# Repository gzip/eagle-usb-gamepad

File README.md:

# Classic Gamepad USB Adapter

This hardware and software allows you to connect your favorite classic gamepad to use as a joystick on your computer. The design is based on work from [raphnet.net](http://raphnet.net/electronique/electronique_en.php#1) and is completely open. The following configurations are supported:

- Four NES and/or SNES gamepads
- One N64 or Gamecube gamepad
- One Genesis or Atari gamepad

Connector footprints are also available for NES, SNES, and N64 under the [breakouts](./breakouts/) folder.

# Availability

Boards available at [OSH Park](https://www.oshpark.com/shared_projects/oCdHAtTx).

Kits available at [Tindie](https://www.tindie.com/products/gzip/classic-gamepad-usb-adapter/).

## License

All hardware and software is derivative of raphnet.net and is therefore GPL. The [breakout boards](./breakouts/) are original works and licensed under [Creative Commons Share Alike](http://creativecommons.org/licenses/by-sa/4.0/).

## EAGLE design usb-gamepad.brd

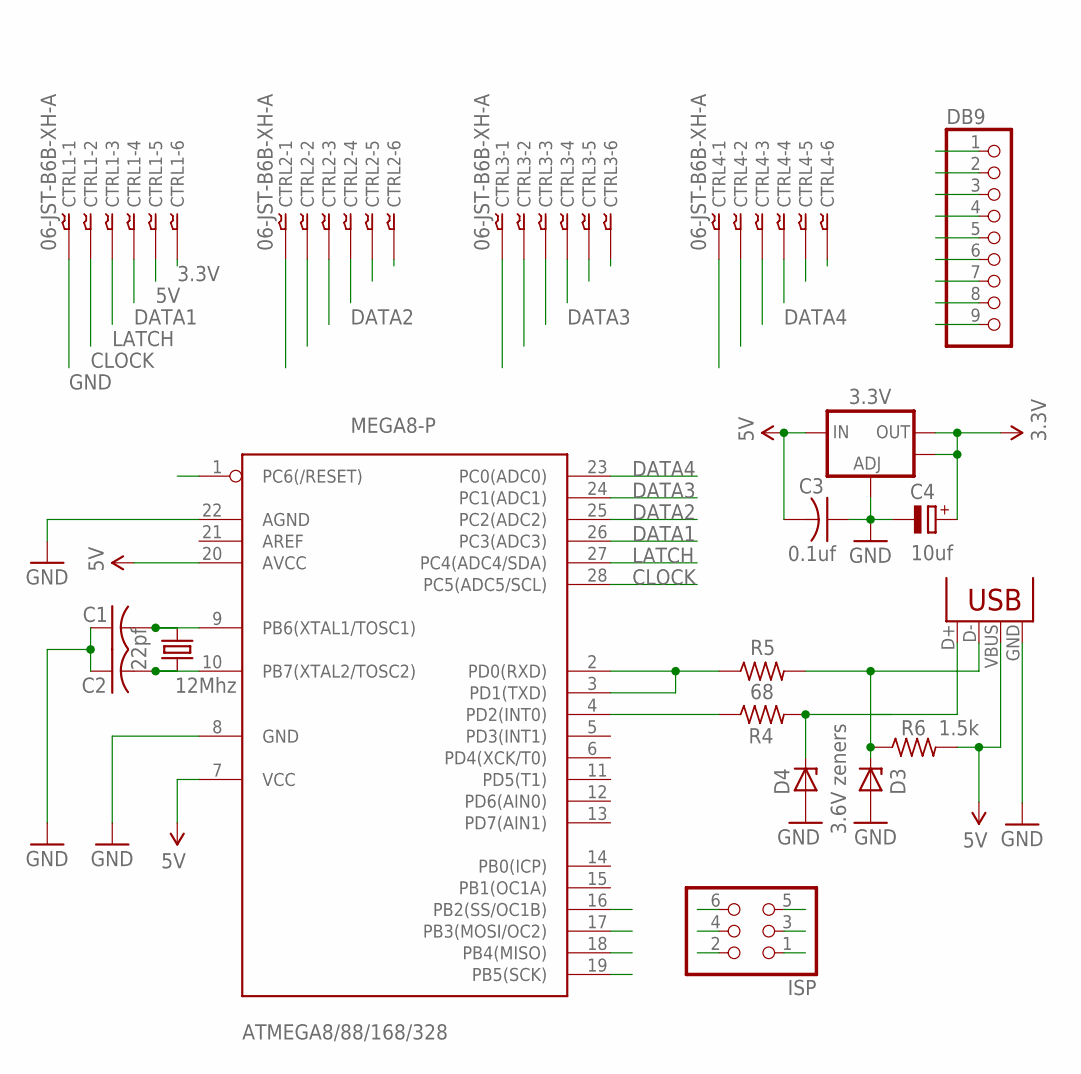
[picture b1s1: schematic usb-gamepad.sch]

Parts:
3.3V: V_REG_LM1117SOT223; SOT223
ATMEGA8/88/168/328: MEGA8-P; DIL28-3
C1, C2: 22pf; C025-025X050
C3: 0.1uf; C025-025X050
C4: 10uf; E2,5-5
CTRL1, CTRL2, CTRL3, CTRL4: 06-JST-B6B-XH-A; B6B-XH
D3: 3.6V zeners; DO41Z10
D4: 3.6V; DO41Z10
DB9: PINHD-1X9; 1X09
ISP: PINHD-2X3; 2X03
Q1: 12Mhz; HC49/S
R4, R5: 68; 0207/10
R6: 1.5k; 0207/10
USB: USBPTH; USB-B-PTH

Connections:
3.3V: 3.3V.2 (OUT), 3.3V.4 (OUT), C4.+, CTRL1.P$6, CTRL2.P$6, CTRL3.P$6, CTRL4.P$6
5V: 3.3V.3 (IN), ATMEGA8/88/168/328.7 (VCC), ATMEGA8/88/168/328.20 (AVCC), C3.2, CTRL1.P$5, CTRL2.P$5, CTRL3.P$5, CTRL4.P$5, DB9.5, ISP.2, R6.2, USB.VBUS
CLOCK: ATMEGA8/88/168/328.28 (PC5(ADC5/SCL)), CTRL1.P$2, CTRL2.P$2, CTRL3.P$2, CTRL4.P$2, DB9.1
D+: D4.C, R4.2, USB.D+
D-: D3.C, R5.2, R6.1, USB.D-
DATA1: ATMEGA8/88/168/328.26 (PC3(ADC3)), CTRL1.P$4, DB9.3
DATA2: ATMEGA8/88/168/328.25 (PC2(ADC2)), CTRL2.P$4, DB9.4
DATA3: ATMEGA8/88/168/328.24 (PC1(ADC1)), CTRL3.P$4, DB9.6
DATA4: ATMEGA8/88/168/328.23 (PC0(ADC0)), CTRL4.P$4, DB9.7
GND: 3.3V.1 (ADJ), ATMEGA8/88/168/328.8 (GND), ATMEGA8/88/168/328.22 (AGND), C1.1, C2.1, C3.1, C4.-, CTRL1.P$1, CTRL2.P$1, CTRL3.P$1, CTRL4.P$1, D3.A, D4.A, DB9.8, ISP.6, USB.GND
LATCH: ATMEGA8/88/168/328.27 (PC4(ADC4/SDA)), CTRL1.P$3, CTRL2.P$3, CTRL3.P$3, CTRL4.P$3, DB9.2
MISO: ATMEGA8/88/168/328.18 (PB4(MISO)), ISP.1
MOSI: ATMEGA8/88/168/328.17 (PB3(MOSI/OC2)), ISP.4
unnamed: ATMEGA8/88/168/328.10 (PB7(XTAL2/TOSC2)), C2.2, Q1.1
unnamed: ATMEGA8/88/168/328.9 (PB6(XTAL1/TOSC1)), C1.2, Q1.2
unnamed: ATMEGA8/88/168/328.2 (PD0(RXD)), ATMEGA8/88/168/328.3 (PD1(TXD)), R5.1
unnamed: ATMEGA8/88/168/328.4 (PD2(INT0)), R4.1
RESET: ATMEGA8/88/168/328.1 (PC6(/RESET)), ISP.5
SCK: ATMEGA8/88/168/328.19 (PB5(SCK)), DB9.9, ISP.3
SS: ATMEGA8/88/168/328.16 (PB2(SS/OC1B))

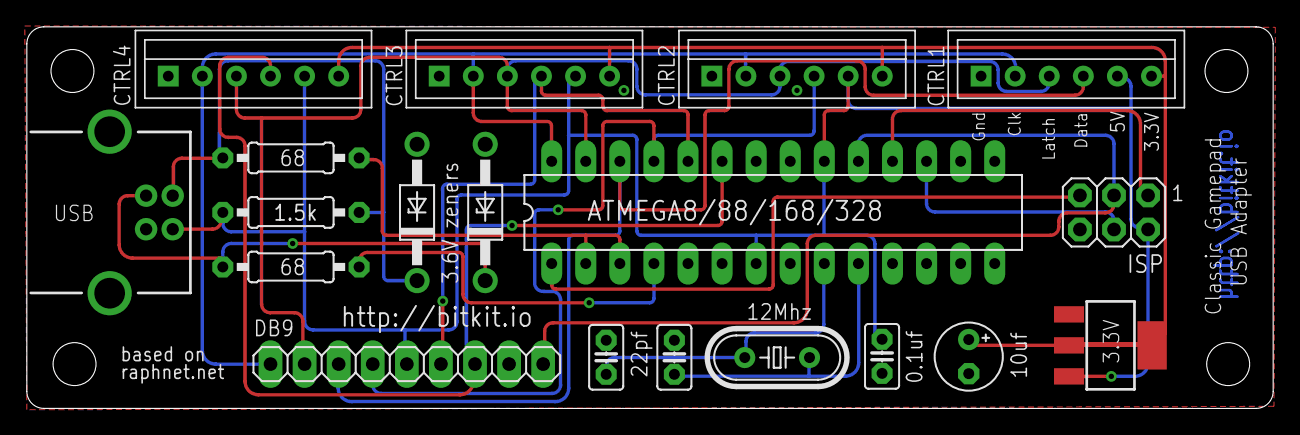
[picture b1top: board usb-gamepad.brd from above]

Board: 2 copper layers, 92.9 x 28.4 mm, 19 parts (0 on the bottom side), 19 nets.

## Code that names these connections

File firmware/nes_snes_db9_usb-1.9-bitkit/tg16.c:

/* TG16 to USB
 * Copyright (C) 2006-2011 Raphaël Assénat
 *
 * This program is free software; you can redistribute it and/or modify
 * it under the terms of the GNU General Public License as published by
 * the Free Software Foundation; either version 2 of the License, or
 * (at your option) any later version.
 *
 * This program is distributed in the hope that it will be useful,
 * but WITHOUT ANY WARRANTY; without even the implied warranty of
 * MERCHANTABILITY or FITNESS FOR A PARTICULAR PURPOSE.  See the
 * GNU General Public License for more details.
 *
 * You should have received a copy of the GNU General Public License along
 * with this program; if not, write to the Free Software Foundation, Inc.,
 * 51 Franklin Street, Fifth Floor, Boston, MA 02110-1301 USA.
 *
 * The author may be contacted at raph@raphnet.net
 */
#include <avr/io.h>
#include <avr/interrupt.h>
#include <avr/pgmspace.h>

#include <util/delay.h>
#include <string.h>

#include "usbdrv.h"
#include "usbconfig.h"
#include "gamepad.h"
#include "leds.h"
#include "tg16.h"

#define REPORT_SIZE		3
#define GAMEPAD_BYTES	3

/* for chaning IO easily */


#define SET_SELECT()	PORTC |= 0x02
#define CLR_SELECT()	PORTC &= ~0x02

/* Active low */
#define SET_OE()		PORTC &= ~0x01
#define CLR_OE()		PORTC |= 0x01


/*********** prototypes *************/
static char tg16_Init(void);
static void tg16_Update(void);

// the most recent bytes we fetched from the controller
static unsigned char last_read_controller_bytes[REPORT_SIZE];
// the most recently reported bytes
static unsigned char last_reported_controller_bytes[REPORT_SIZE];

static unsigned char readController()
{
	unsigned char a,b;

	/* 
	 * --- tg16 specific pinout ---
	 *  inputs...
	 * PC5: /Up or /I
	 * PC4: /Right or /II
	 * PC3: /South or /Select
	 * PC2: /Left or /Run
	 *
	 *  outputs...
	 * PC1: Data select
	 * PC0: /OE
	 */

	SET_OE();
	_delay_ms(1);

	SET_SELECT();
	_delay_ms(1);
	a = (PINC & 0x3c) >> 2;

	CLR_SELECT();
	_delay_ms(1);		
	b = (PINC & 0x3c) >> 2;

	CLR_OE();

	return a | (b<<4);
}

static char tg16_Init(void)
{
	unsigned char sreg;
	sreg = SREG;
	cli();

	DDRB |= 0x02; // Bit 1 out
	PORTB &= ~0x02; // 0

	/* 
	 * --- tg16 specific pinout ---
	 *  inputs...
	 * PC5: /Up or /I
	 * PC4: /Right or /II
	 * PC3: /South or /Select
	 * PC2: /Left or /Run
	 *
	 *  outputs...
	 * PC1: Data select
	 * PC0: /OE
	 */

	DDRC &= ~0x3c; 
	PORTC |= 0x3c;

	/* disable OE and init DataSelect to 1 */
	PORTC |= 0x03;
	DDRC |= 0x03;
	
	tg16_Update();

	SREG = sreg;

	return 0;
}



static void tg16_Update(void)
{
	unsigned char data;
	int x=128,y=128;
	
	/* 7: I
	 * 6: II
	 * 5: Select
	 * 4: Run
	 *
	 * 3: Up
	 * 2: Right
	 * 1: Down
	 * 0: Left
	 */
	data = readController();

	/* Buttons are active low. Invert values. */
	data ^= 0xff;

	if (data & 0x08) { y = 0; } // up
	if (data & 0x02) { y = 255; } //down
	if (data & 0x01) { x = 0; }  // left
	if (data & 0x04) { x = 255; } // right

	last_read_controller_bytes[0]=x;
	last_read_controller_bytes[1]=y;
 
 	last_read_controller_bytes[2]=0;

	if (data & 0x80) 
		last_read_controller_bytes[2] |= 0x01;
	if (data & 0x40)
		last_read_controller_bytes[2] |= 0x02;
	if (data & 0x20)
		last_read_controller_bytes[2] |= 0x04;
	if (data & 0x10)
		last_read_controller_bytes[2] |= 0x08;

}	

static char tg16_Changed(char id)
{
	static int first = 1;
	if (first) { first = 0;  return 1; }
	
	return memcmp(last_read_controller_bytes, 
					last_reported_controller_bytes, GAMEPAD_BYTES);
}

static char tg16_BuildReport(unsigned char *reportBuffer, char id)
{
	if (reportBuffer != NULL)
	{
		memcpy(reportBuffer, last_read_controller_bytes, GAMEPAD_BYTES);
	}
	memcpy(last_reported_controller_bytes, 
			last_read_controller_bytes, 
			GAMEPAD_BYTES);	

	return REPORT_SIZE;
}

#include "snes_descriptor.c"

#define USBDESCR_DEVICE         1

// This is the same descriptor as in devdesc.c, but with a different VID/PID

const char tg16_usbDescrDevice[] PROGMEM = {    /* USB device descriptor */
    18,         /* sizeof(usbDescrDevice): length of descriptor in bytes */
    USBDESCR_DEVICE,    /* descriptor type */
    0x01, 0x01, /* USB version supported */
    USB_CFG_DEVICE_CLASS,
    USB_CFG_DEVICE_SUBCLASS,
    0,          /* protocol */
    8,          /* max packet size */
    0x40, 0x17,  /* 2 bytes vendor id*/
    0x7a, 0x05,  /* 2 bytes */
    USB_CFG_DEVICE_VERSION, /* 2 bytes */
    USB_CFG_DESCR_PROPS_STRING_VENDOR != 0 ? 1 : 0,         /* manufacturer string index */
    USB_CFG_DESCR_PROPS_STRING_PRODUCT != 0 ? 2 : 0,        /* product string index */
    USB_CFG_DESCR_PROPS_STRING_SERIAL_NUMBER != 0 ? 3 : 0,  /* serial number string index */
    1,          /* number of configurations */
};

Gamepad tg16_Gamepad = {
	.num_reports			=	1,
	.reportDescriptorSize	=	sizeof(snes_usbHidReportDescriptor),
	.deviceDescriptorSize	=	sizeof(tg16_usbDescrDevice),
	.init					=	tg16_Init,
	.update					=	tg16_Update,
	.changed				=	tg16_Changed,
	.buildReport			=	tg16_BuildReport
};

Gamepad *tg16_GetGamepad(void)
{
	tg16_Gamepad.reportDescriptor = (void*)snes_usbHidReportDescriptor;
	tg16_Gamepad.deviceDescriptor = (void*)tg16_usbDescrDevice;

	return &tg16_Gamepad;
}

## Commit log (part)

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2014-11-18 Remove
2014-11-18 Add gerbers folder
2014-11-18 Add gerbers readme
2014-11-26 Add oshpark link and add license for breakouts
